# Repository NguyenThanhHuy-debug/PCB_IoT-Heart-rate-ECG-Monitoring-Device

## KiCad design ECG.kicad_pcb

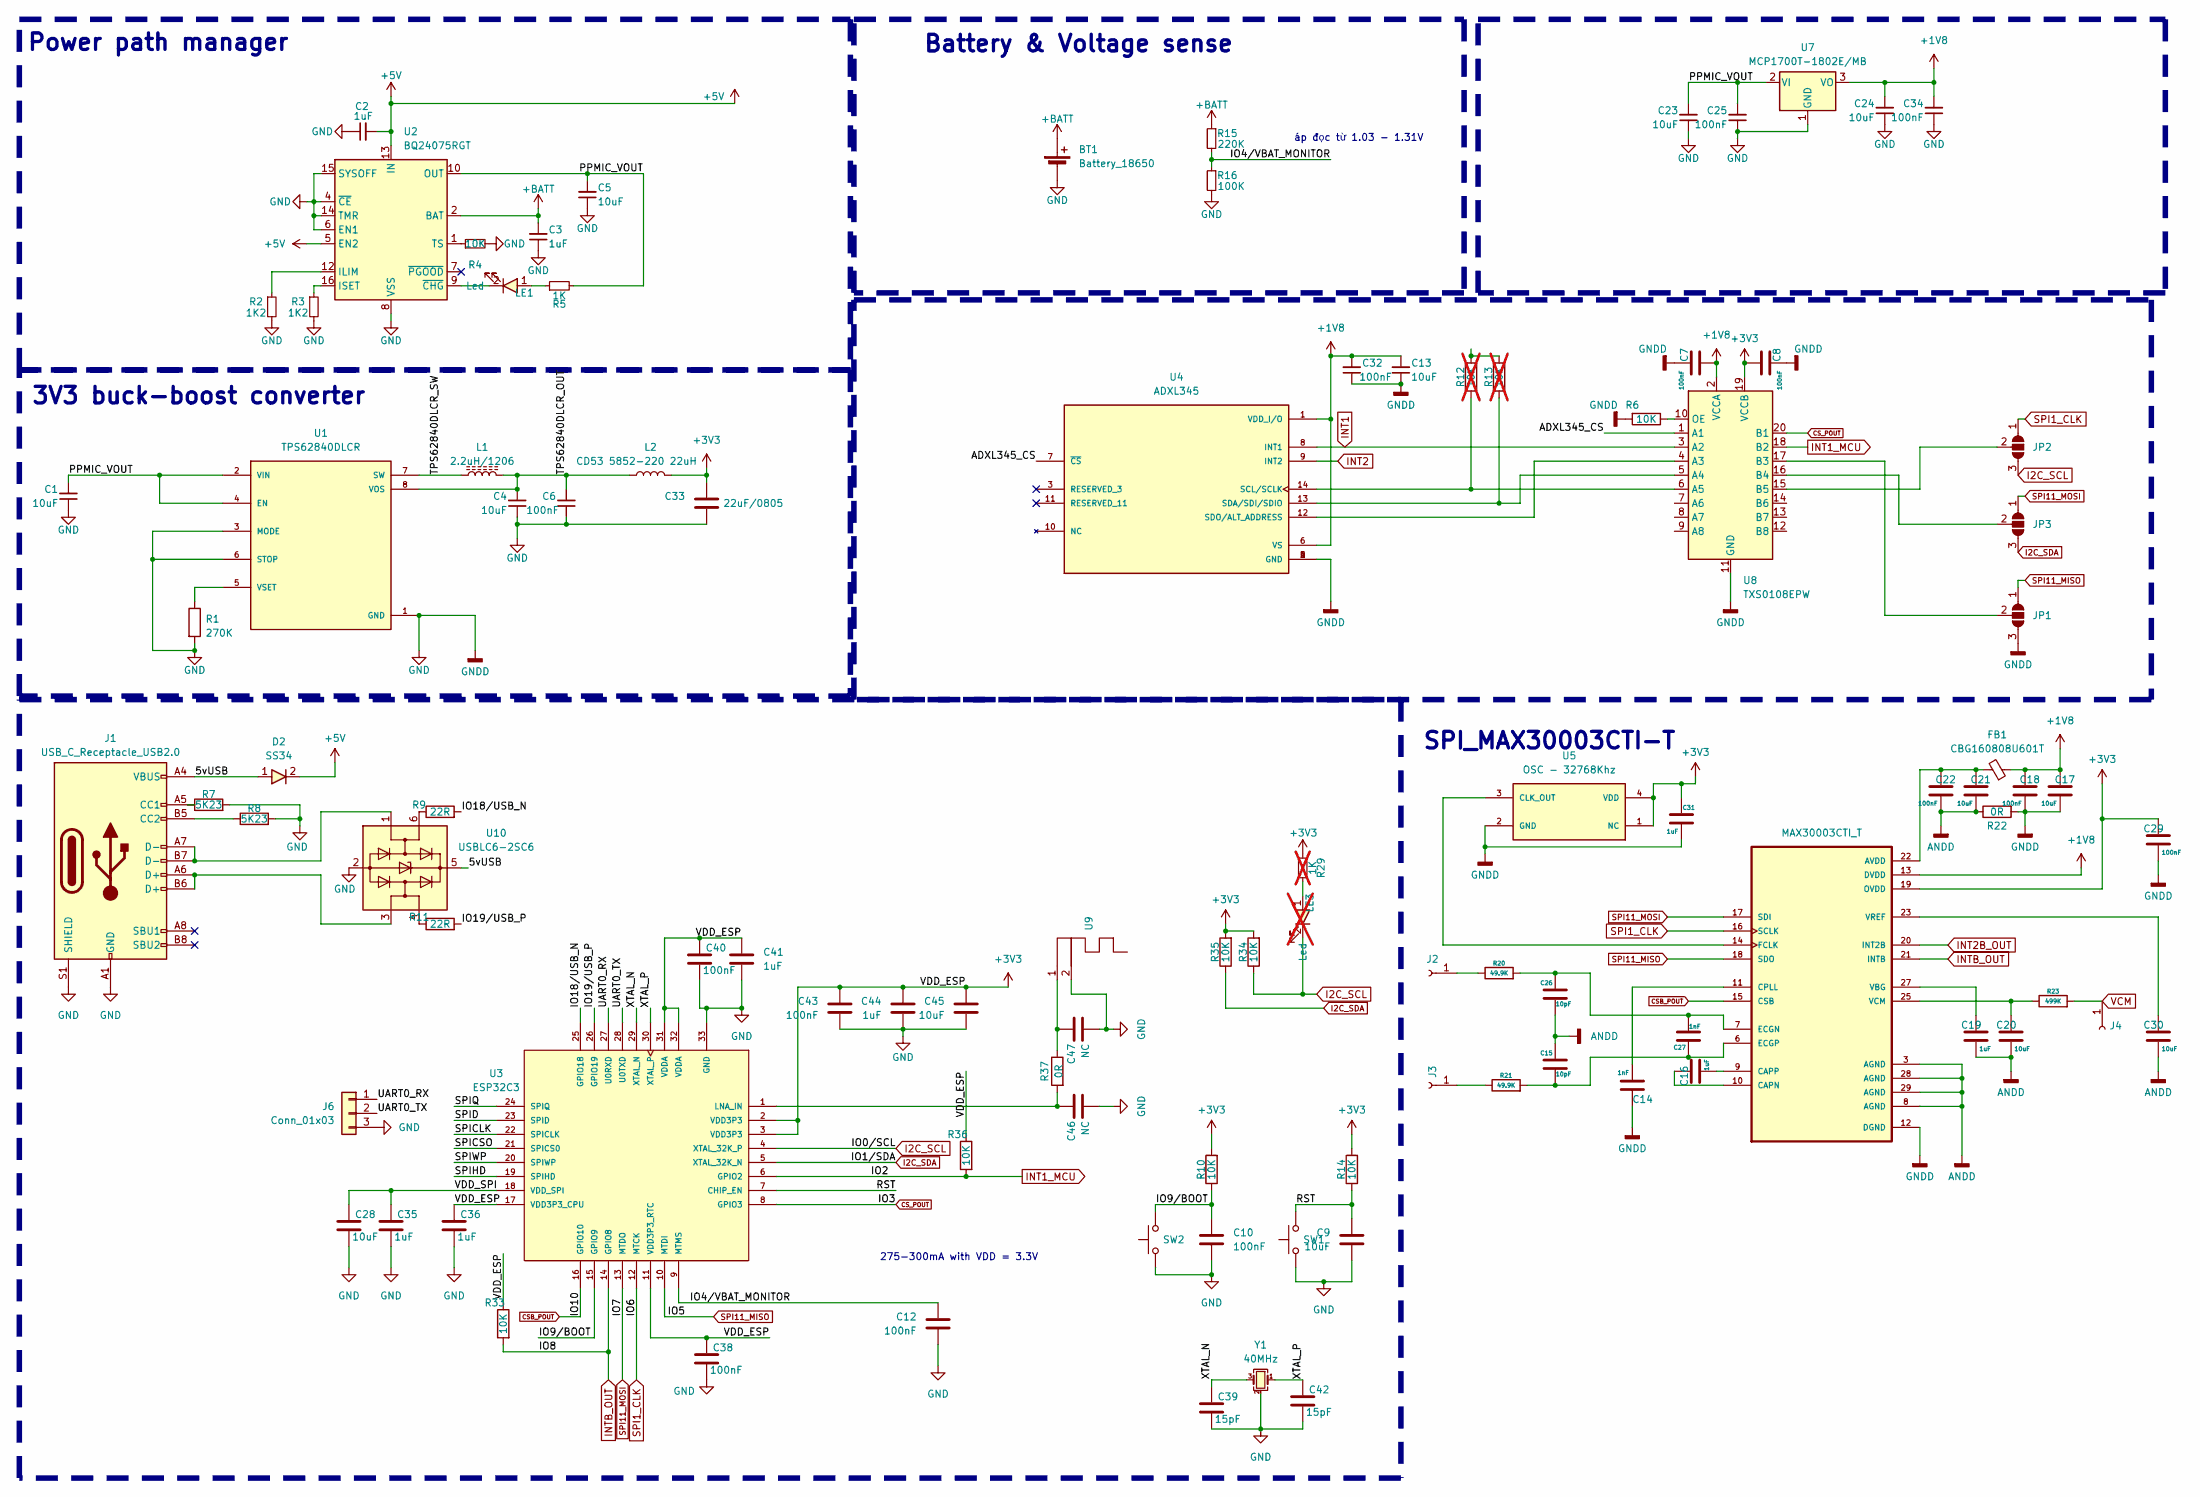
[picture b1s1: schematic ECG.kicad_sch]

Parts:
BT1: Battery_18650; PH_2.0mm_DIP
C1, C4, C5, C13, C17, C20, C21, C23, C24, C30: 10uF; C_0603
C2, C3, C16, C19, C31: 1uF; C_0603
C6, C7, C8, C25, C29, C32, C34: 100nF; C_0402_1005Metric
C9: 10uF; C_0603; MFR Part CL10B104KC8NNNC
C10, C12: 100nF; C_0402_1005Metric; MFR Part CL10B104KC8NNNC
C14, C27: 1nF; C_0402_1005Metric
C15, C26: 10pF; C_0603
C18, C22: 100nF; C_0603
C28, C45: 10uF; C_0603; MANUFACTURER PART Samsung Electro-Mechanics
C33: 22uF/0805; C_0805
C35, C36, C41, C44: 1uF; C_0603; MANUFACTURER PART Samsung Electro-Mechanics
C38, C40, C43: 100nF; C_0402_1005Metric; MANUFACTURER PART Samsung Electro-Mechanics
C39, C42: 15pF; C_0402_1005Metric; MANUFACTURER PART Samsung Electro-Mechanics
C46, C47: NC; C_0402_1005Metric
D2: SS34; D_SMA; MFR Part SS34
FB1: CBG160808U601T; R_0603
J1: USB_C_Receptacle_USB2.0; USB_C_Receptacle_XKB_U262-16XN-4BVC11; MFR Part 1332645
J2, J3: Conn_01x01_Socket; MountingHole_4.3mm_M4_Pad_Via
J4: Conn_01x01_Socket; PinSocket_1x01_P2.54mm_Vertical
J6: Conn_01x03; PinHeader_1x03_P2.00mm_Vertical
JP1, JP2, JP3: SolderJumper_3_Open; Jump3_0603_Open
L1: 2.2uH/1206; L_1206
L2: CD53 5852-220 22uH; L_0805
LE1: Led; LED_0603
LE3: Led; LED_0603; not fitted
R1: 270K; R_0402_1005Metric
R2, R3: 1K2; R_0402_1005Metric
R4: 10K; R_0402_1005Metric
R5: 1K; R_0402_1005Metric
R6, R10, R14, R34, R35: 10K; R_0402_1005Metric; MFR Part CRCW060310K0FKEA
R7, R8: 5K23; R_0402_1005Metric; MFR Part CRCW06035K10FKEAC
R9, R11: 22R; R_0402_1005Metric; MFR Part CRCW06035K10FKEAC
R12, R13: 10K; R_0402_1005Metric; MFR Part CRCW060310K0FKEA; not fitted
R15: 220K; R_0402_1005Metric
R16: 100K; R_0402_1005Metric
R20, R21: 49.9K; R_0603
R22: 0R; R_0603; MFR Part CRCW060310K0FKEA
R23: 499K; R_0603
R29: 1K; R_0402_1005Metric; not fitted
R33, R36: 10K; R_0402_1005Metric; MANUFACTURER PART Vishay Dale
R37: 0R; R_0402_1005Metric; MANUFACTURER PART Panasonic Electronic Components
SW1, SW2: SW_Tactile; SW_SPST_B3U-1000P; MFR Part B3U-1000P
U1: TPS62840DLCR; VSON-HR - 1 mm
U2: BQ24075RGT; VQFN-16-1EP_3x3mm_P0.5mm_EP1.6x1.6mm_ThermalVias
U3: ESP32C3; QFN32_5X5MM; MANUFACTURER PART Espressif Systems
U4: ADXL345; PARTREV B
U5: OSC - 32768Khz; RTC-XTAL
U6: MAX30003CTI_T; MAX30003CTI+T
U7: MCP1700T-1802E/MB; SOT-89-3
U8: TXS0108EPW; TSSOP-20_4.4x6.5mm_P0.65mm
U9: Texas_SWRA117D_2.4GHz_Left
U10: USBLC6-2SC6; SOT-23-6
Y1: 40MHz; Crystal_3225_4P_3.2x2.6mm; MANUFACTURER PART KYOCERA AVX

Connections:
+1V8: C7.2, C13.2, C17.1, C18.1, C24.2, C32.2, C34.2, FB1.1, U4.1 (VDD_I/O), U4.6 (VS), U6.13 (DVDD), U7.3 (VO), U8.2 (VCCA)
+3V3: C8.2, C29.1, C31.1, C33.1, C36.1, C38.1, C40.1, C41.1, C43.1, C44.1, C45.1, L2.2, R10.2, R14.2, R29.2, R33.1, R34.2, R35.2, R36.1, U3.2 (VDD3P3), U3.3 (VDD3P3), U3.11 (VDD3P3_RTC), U3.17 (VDD3P3_CPU), U3.31 (VDDA), U3.32 (VDDA), U5.1 (NC), U5.4 (VDD), U6.19 (OVDD), U8.19 (VCCB)
+5V: C2.2, D2.2, U2.5 (EN2), U2.13 (IN)
+BATT: BT1.1 (+), C3.2, R15.1, U2.2 (BAT), U2.3 (BAT)
/5vUSB: D2.1, J1.A4 (VBUS), J1.A9 (VBUS), J1.B4 (VBUS), J1.B9 (VBUS), U10.5 (VBUS)
/ADXL345_CS: U4.7 (~CS), U8.1 (A1)
/IO4/VBAT_MONITOR: C12.1, R15.2, R16.1, U3.9 (MTMS)
/IO9/BOOT: C10.1, R10.1, SW2.2, U3.15 (GPIO9)
/IO18/USB_N: R9.2, U3.25 (GPIO18)
/IO19/USB_P: R11.2, U3.26 (GPIO19)
/PPMIC_VOUT: C1.2, C5.2, C23.2, C25.2, R5.2, U1.2 (VIN), U1.4 (EN), U2.10 (OUT), U2.11 (OUT), U7.2 (VI)
/RST: C9.1, R14.1, SW1.2, U3.7 (CHIP_EN)
/SPICLK: U3.22 (SPICLK)
/SPICSO: U3.21 (SPICS0)
/SPID: U3.23 (SPID)
/SPIHD: U3.19 (SPIHD)
/SPIQ: U3.24 (SPIQ)
/SPIWP: U3.20 (SPIWP)
/TPS62840DLCR_OUT: C4.2, C6.2, L1.2, L2.1, U1.8 (VOS)
/TPS62840DLCR_SW: L1.1, U1.7 (SW)
/UART0_RX: J6.1, U3.27 (U0RXD)
/UART0_TX: J6.2, U3.28 (U0TXD)
/VDD_SPI: C28.1, C35.1, U3.18 (VDD_SPI)
/XTAL_N: C39.1, U3.29 (XTAL_N), Y1.3
/XTAL_P: C42.1, U3.30 (XTAL_P), Y1.1
ANDD: C15.1, C19.2, C20.2, C21.2, C22.2, C26.2, C30.2, R22.1, U6.3 (AGND), U6.8 (AGND), U6.28 (AGND), U6.29 (AGND)
CSB_POUT: U3.16 (GPIO10), U6.15 (CSB)
CS_POUT: U3.8 (GPIO3), U8.20 (B1)
GND: BT1.2 (-), C1.1, C2.1, C3.1, C4.1, C5.1, C6.1, C7.1, C8.1, C9.2, C10.2, C12.2, C13.1, C14.1, C17.2, C18.2, C23.1, C24.1, C25.1, C28.2, C29.2, C31.2, C32.1, C33.2, C34.1, C35.2, C36.2, C38.2, C39.2, C40.2, C41.2, C42.2, C43.2, C44.2, C45.2, C46.2, C47.2, J1.A1 (GND), J1.A12 (GND), J1.B1 (GND), J1.B12 (GND), J1.S1 (SHIELD), J6.3, JP1.3 (B), R1.2, R2.2, R3.2, R4.2, R6.2, R7.2, R8.2, R16.2, R22.2, SW1.1, SW2.1, U1.1 (GND), U1.3 (MODE), U1.6 (STOP), U2.4 (~CE), U2.6 (EN1), U2.8 (VSS), U2.14 (TMR), U2.15 (SYSOFF), U2.17 (VSS), U3.33 (GND), U4.2 (GND), U4.4 (GND), U4.5 (GND), U5.2 (GND), U6.12 (DGND), U7.1 (GND), U8.11 (GND), U9.2, U10.2 (GND), Y1.2, Y1.4
I2C_SCL: JP2.3 (B), LE3.2, R34.1, U3.4 (XTAL_32K_P)
I2C_SDA: JP3.3 (B), R35.1, U3.5 (XTAL_32K_N)
INT1: U4.8 (INT1), U8.3 (A2)
INT1_MCU: R36.2, U3.6 (GPIO2), U8.18 (B2)
INT2: U4.9 (INT2)
INT2B_OUT: U6.20 (INT2B)
INTB_OUT: R33.2, U3.14 (GPIO8), U6.21 (INTB)
unnamed: C47.1, R37.1, U9.1
unnamed: J1.A5 (CC1), R7.1
unnamed: J1.B5 (CC2), R8.1
unnamed: J1.A6 (D+), J1.B6 (D+), U10.3 (I/O2)
unnamed: J1.A7 (D-), J1.B7 (D-), U10.1 (I/O1)
unnamed: J2.1, R20.1
unnamed: J3.1, R21.1
unnamed: JP1.2 (C), U8.17 (B3)
unnamed: JP2.2 (C), U8.15 (B5)
unnamed: JP3.2 (C), U8.16 (B4)
unnamed: LE1.1, R5.1
unnamed: LE3.1, R29.1
unnamed: R9.1, U10.6 (I/O1)
unnamed: R11.1, U10.4 (I/O2)
unnamed: R12.2, R13.2
unnamed: R1.1, U1.5 (VSET)
unnamed: R2.1, U2.12 (ILIM)
unnamed: R3.1, U2.16 (ISET)
unnamed: R4.1, U2.1 (TS)
unnamed: LE1.2, U2.9 (~CHG)
unnamed: C46.1, R37.2, U3.1 (LNA_IN)
unnamed: R12.1, U4.14 (SCL/SCLK), U8.6 (A5)
unnamed: R13.1, U4.13 (SDA/SDI/SDIO), U8.5 (A4)
unnamed: U4.12 (SDO/ALT_ADDRESS), U8.4 (A3)
unnamed: U5.3 (CLK_OUT), U6.14 (FCLK)
unnamed: C21.1, C22.1, FB1.2, U6.22 (AVDD)
unnamed: C16.1, U6.10 (CAPN)
unnamed: C16.2, U6.9 (CAPP)
unnamed: C14.2, U6.11 (CPLL)
unnamed: C26.1, C27.2, R20.2, U6.7 (ECGN)
unnamed: C15.2, C27.1, R21.2, U6.6 (ECGP)
unnamed: C19.1, U6.27 (VBG)
unnamed: C20.1, R23.1, U6.25 (VCM)
unnamed: C30.1, U6.23 (VREF)
unnamed: R6.1, U8.10 (OE)
SPI1_CLK: JP2.1 (A), U3.12 (MTCK), U6.16 (SCLK)
SPI11_MISO: JP1.1 (A), U3.10 (MTDI), U6.18 (SDO)
SPI11_MOSI: JP3.1 (A), U3.13 (MTDO), U6.17 (SDI)
VCM: J4.1, R23.2

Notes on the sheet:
275-300mA with VDD = 3.3V
3V3 buck-boost converter
Power path manager
SPI_MAX30003CTI-T
Battery & Voltage sense
áp đọc từ 1.03 - 1.31V

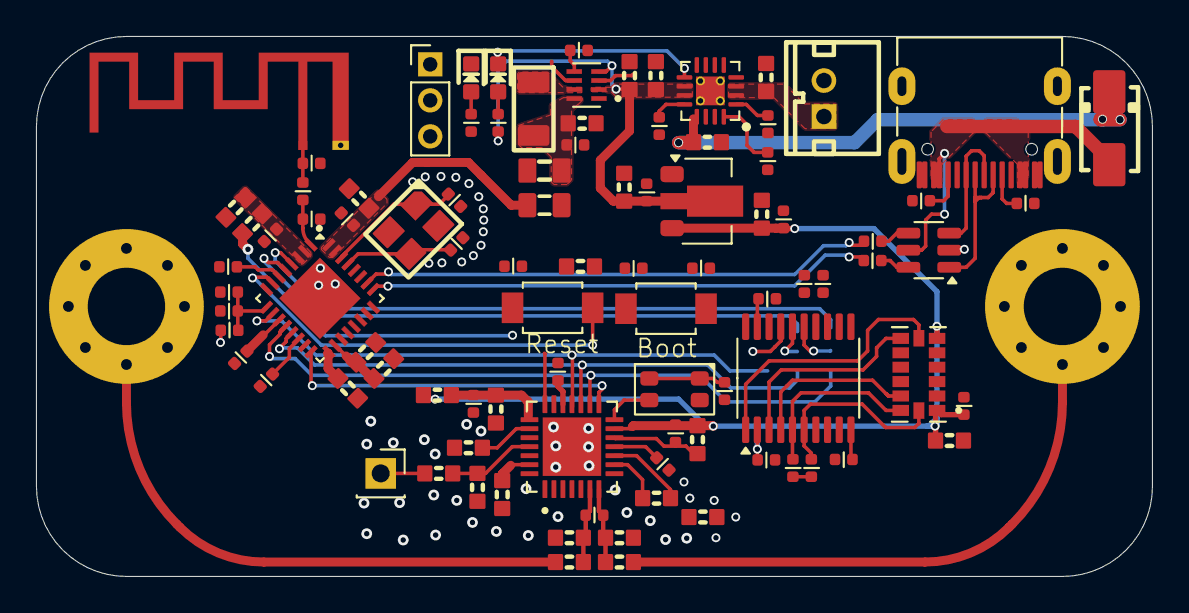
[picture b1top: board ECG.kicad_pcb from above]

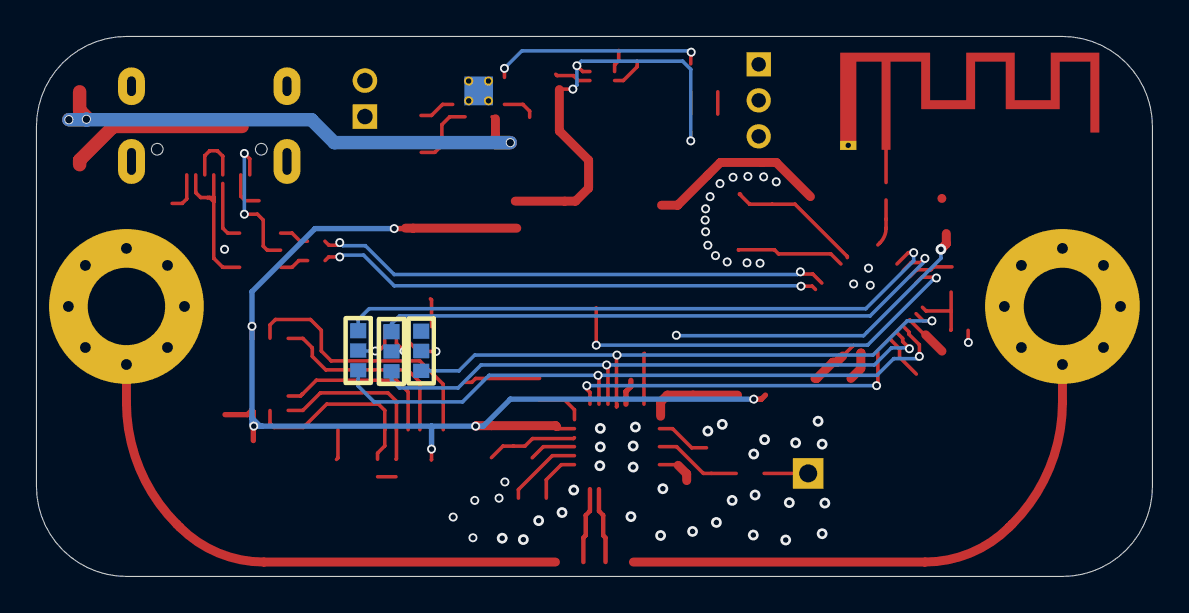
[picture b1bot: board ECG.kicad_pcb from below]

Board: 2 copper layers, 62.0 x 30.0 mm, 99 parts (3 on the bottom side), 67 nets.
